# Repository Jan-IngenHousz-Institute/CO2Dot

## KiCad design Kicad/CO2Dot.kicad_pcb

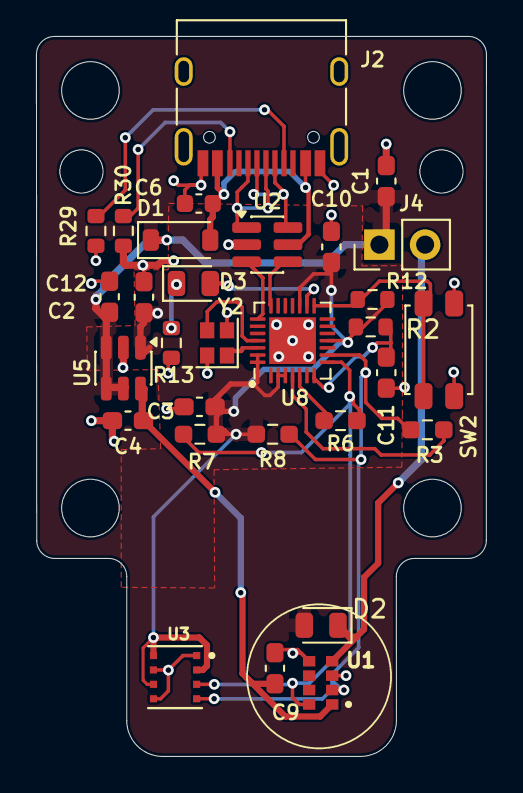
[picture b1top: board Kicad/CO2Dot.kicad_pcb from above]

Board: 4 copper layers, 25.0 x 40.0 mm, 30 parts (0 on the bottom side), 22 nets.

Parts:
C1, C2, C3, C4, C9, C10, C11, C12: 2.2u; C_0603_1608Metric_Pad1.08x0.95mm_HandSolder
C6: 10u; C_0603_1608Metric
D1: 1N4148WT; D_SOD-123
D2, D3: LED; D_0805_2012Metric
J2: USB_C_Receptacle; USB_C_Receptacle_HRO_TYPE-C-31-M-12
J4: Conn_01x02_Pin; PinHeader_1x02_P2.54mm_Vertical
R2, R12, R13, R29, R30: 5.1K; R_0603_1608Metric
R3, R6: 0R; R_0603_1608Metric_Pad0.98x0.95mm_HandSolder
R7, R8: 10K; R_0603_1608Metric_Pad0.98x0.95mm_HandSolder
SW2: SW_Push; SW_SPST_EVQP2_ShortPushTravel_H2.1mm
U1: AS7341-DLGT; PSON80P310X200X110-8N
U2: IP4234CZ6; SC-74-6_1.55x2.9mm_P0.95mm
U3: BME688
U5: AP7312-1833W6-7; TSOT-23-6
U8: ESP8685; QFN-28-1EP_4x4mm_P0.4mm_EP2.6x2.6mm
Y2: 40MHz; Crystal_SMD_2016-4Pin_2.0x1.6mm

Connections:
BOOT: R12.1, SW2.1, U8.15 (GPIO9/BOOT)
CC1: J2.A5 (CC1), R29.2
CC2: J2.B5 (CC2), R30.2
D+: U2.3, U8.22 (GPIO19/USB_D+)
D-: U2.4, U8.21 (GPIO18/USB_D-)
GND: C1.2, C2.2, C3.2, C4.2, C6.1, C9.2, C10.2, C11.2, C12.2, J2.A1 (GND), J2.A12 (GND), J2.B1 (GND), J2.B12 (GND), J2.S1 (SHIELD), R13.1, R29.1, R30.1, SW2.2, U1.3 (GND), U1.5 (PGND), U2.2 (VN), U3.1 (GND), U3.5 (SDO), U3.7 (GND__1), U5.2 (GND), U8.29 (GND), Y2.2, Y2.4
LED1ACT: D2.1 (K), J4.2, U1.4 (LDR)
unnamed: D3.2 (A), U8.16 (GPIO10)
unnamed: D3.1 (K), R13.2
unnamed: J2.A6 (D+), J2.B6 (D+), U2.1
unnamed: J2.A7 (D-), J2.B7 (D-), U2.6
unnamed: U8.25 (XTAL_N), Y2.3
unnamed: U8.26 (XTAL_P), Y2.1
SCL: R3.2, R8.1, U1.2 (SCL), U3.4 (SCK), U8.9 (MTMS/GPIO4/ADC1_CH4)
SCL_2: R6.1, U8.5 (GPIO1/XTAL_32K_N/ADC1_CH1)
SDA: R6.2, R7.1, U1.8 (SDA), U3.3 (SDI), U8.8 (GPIO3/ADC1_CH3)
SDA_2: R3.1, U8.4 (GPIO0/XTAL_32K_P/ADC1_CH0)
V+: C1.1, C12.1, D1.1 (K), D2.2 (A), J4.1, U5.3 (EN2), U5.4 (EN1), U5.5 (VIN)
V+1.8V: C4.1, C9.1, U1.1 (VDD), U5.6 (VOUT_1V8)
V+3V: C2.1, C3.1, C10.1, R2.1, R7.2, R8.2, R12.2, U3.2 (CSB), U3.6 (VDDIO), U3.8 (VDD), U5.1 (VOUT_3V3), U8.2 (VDD3P3), U8.3 (VDD3P3), U8.11 (VDD3P3_RTC), U8.17 (VDD3P3_CPU), U8.27 (VDDA), U8.28 (VDDA)
Vusb: C6.2, D1.2 (A), J2.A4 (VBUS), J2.A9 (VBUS), J2.B4 (VBUS), J2.B9 (VBUS), U2.5 (VP)
reset_EN: C11.1, R2.2, U8.7 (CHIP_EN)

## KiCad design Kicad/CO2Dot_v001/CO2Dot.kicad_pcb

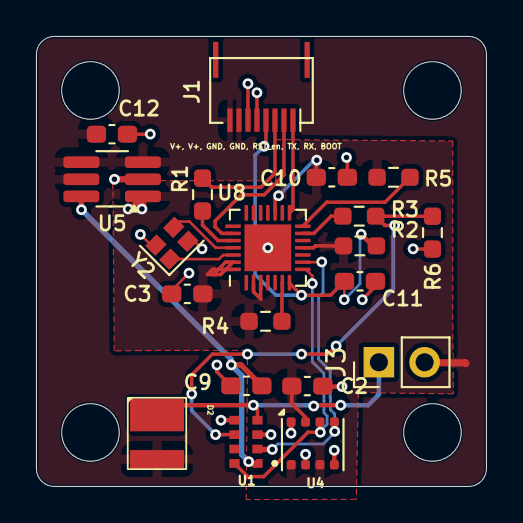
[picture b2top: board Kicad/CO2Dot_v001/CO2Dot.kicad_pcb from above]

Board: 4 copper layers, 25.0 x 25.0 mm, 20 parts (0 on the bottom side), 18 nets.

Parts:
C2, C9: 100n; C_0603_1608Metric_Pad1.08x0.95mm_HandSolder
C3, C10, C11, C12: 2.2u; C_0603_1608Metric_Pad1.08x0.95mm_HandSolder
D2: LED; NF2W757GT-F1
J1: Conn_01x08; Molex_5034800800_1x08-1MP_P0.50mm_Horizontal
J3: Conn_01x02_Socket; PinHeader_1x02_P2.54mm_Vertical
R1: 500; R_0603_1608Metric_Pad0.98x0.95mm_HandSolder
R2, R3, R4, R5: 10K; R_0603_1608Metric_Pad0.98x0.95mm_HandSolder
R6: 12K; R_0603_1608Metric_Pad0.98x0.95mm_HandSolder
U1: AS7341/3; XDCR_AS7341-DLGM
U4: BME680; Bosch_LGA-8_3x3mm_P0.8mm_ClockwisePinNumbering
U5: AP7312-1833W6-7; TSOT-23-6_HandSoldering
U8: ESP8685; QFN-28-1EP_4x4mm_P0.4mm_EP2.6x2.6mm
Y2: 40MHz; Crystal_SMD_2016-4Pin_2.0x1.6mm

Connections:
BOOT: J1.1, U8.15 (GPIO9/BOOT)
CS: R5.1, U8.14 (GPIO8)
GND: C2.2, C3.2, C9.2, C10.2, C11.2, C12.2, J1.5, J1.6, R6.1, U1.3 (GND), U1.5 (PGND), U4.1 (GND), U4.5 (SDO), U4.7 (GND), U5.2 (GND), U8.29 (GND), Y2.2, Y2.4
LED1ACT: D2.1 (K), J3.1, U1.4 (LDR)
unnamed: R4.1, U8.6 (GPIO2/ADC1_CH2)
unnamed: R3.1, U8.13 (MTDO/GPIO7)
unnamed: R1.1, U8.24 (U0TXD/GPIO21)
unnamed: U8.25 (XTAL_N), Y2.3
unnamed: U8.26 (XTAL_P), Y2.1
Rxd: J1.2, U8.23 (U0RXD/GPIO20)
SCL: U1.2 (SCL), U4.4 (SCK), U8.9 (MTMS/GPIO4/ADC1_CH4)
SDA: U1.8 (SDA), U4.3 (SDI), U8.8 (GPIO3/ADC1_CH3)
SYNC: R3.2, R6.2, U1.6 (GPIO)
Txd: J1.3, R1.2
V+: C12.1, D2.2 (A), J1.7, J1.8, J3.2, U5.3 (EN2), U5.4 (EN1), U5.5 (VIN)
V+1.8V: C9.1, U1.1 (VDD), U5.6 (VOUT_1V8)
V+3V: C2.1, C3.1, C10.1, R2.1, R4.2, R5.2, U4.2 (CSB), U4.6 (VDDIO), U4.8 (VDD), U5.1 (VOUT_3V3), U8.2 (VDD3P3), U8.3 (VDD3P3), U8.11 (VDD3P3_RTC), U8.17 (VDD3P3_CPU), U8.27 (VDDA), U8.28 (VDDA)
reset_EN: C11.1, J1.4, R2.2, U8.7 (CHIP_EN)

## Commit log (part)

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2026-05-03 initial comit
2026-05-06 PCB CO2Dot with BME, V002 (squashed)
2026-05-06 Re-track .gitignore (self-exception)
2026-05-06 PCB CO2Dot with BME, V002
2026-05-07 platformIO usb or uart option
2026-06-19 Apply updated .gitignore (untrack now-ignored files)
2026-06-19 updated licontrol readme
2026-06-19 CO2 series 1st commit
2026-06-19 CO2 series random
2026-06-19 fixed randint
2026-06-19 fix interupt
2026-06-19 fixed iterate temperature script
2026-06-19 nikita's file
2026-06-19 measuring script
2026-06-30 RH fix in li_mqtt.py
2026-06-30 updated to CERN Open Hardware Licence Version 2 - Strongly Reciprocal
